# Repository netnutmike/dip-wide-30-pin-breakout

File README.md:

# dip-wide-30-pin-breakout
A wide 30 pin DIP breakout board designed specifically for nodeMCU dev board but will work with anything.

It is a small board with DIP in the middle and pins on the outside for either pheonix connectors or any other tpye of connection that fits the 2.5mm design specification.

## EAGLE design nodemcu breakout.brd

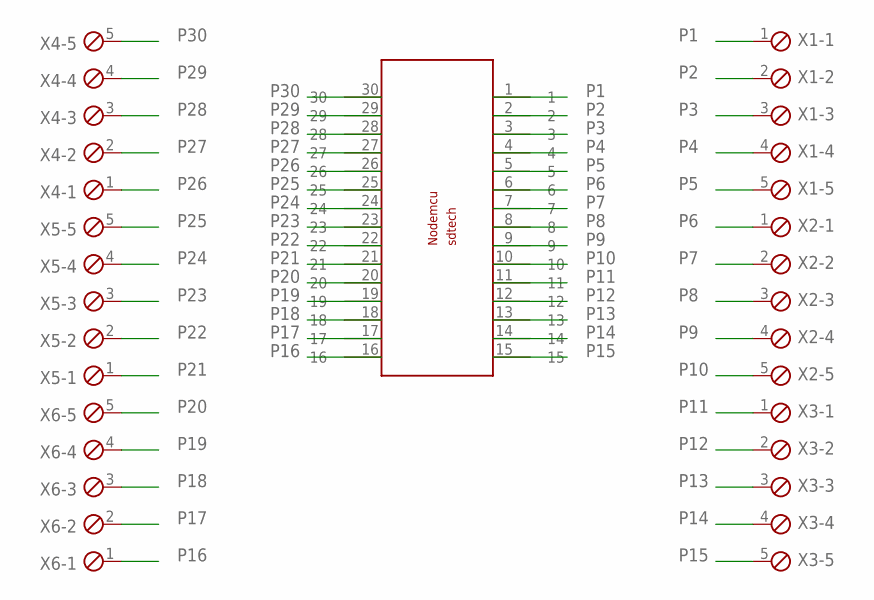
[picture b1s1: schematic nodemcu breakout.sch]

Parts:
U$1: NODEMCUESP8266
X1, X2, X3, X4, X5, X6: MPT5; 5POL254

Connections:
P1: U$1.1, X1.1
P2: U$1.2, X1.2
P3: U$1.3, X1.3
P4: U$1.4, X1.4
P5: U$1.5, X1.5
P6: U$1.6, X2.1
P7: U$1.7, X2.2
P8: U$1.8, X2.3
P9: U$1.9, X2.4
P10: U$1.10, X2.5
P11: U$1.11, X3.1
P12: U$1.12, X3.2
P13: U$1.13, X3.3
P14: U$1.14, X3.4
P15: U$1.15, X3.5
P16: U$1.16, X6.1
P17: U$1.17, X6.2
P18: U$1.18, X6.3
P19: U$1.19, X6.4
P20: U$1.20, X6.5
P21: U$1.21, X5.1
P22: U$1.22, X5.2
P23: U$1.23, X5.3
P24: U$1.24, X5.4
P25: U$1.25, X5.5
P26: U$1.26, X4.1
P27: U$1.27, X4.2
P28: U$1.28, X4.3
P29: U$1.29, X4.4
P30: U$1.30, X4.5

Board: 2 copper layers, 7 parts (0 on the bottom side), 30 nets, no tracks yet.

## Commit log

2020-12-29 Initial Load
2021-01-22 new design from fusion360
2021-04-08 no changes
